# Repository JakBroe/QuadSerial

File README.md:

# QuadSerial
USB Quad Serial Adapter based on FTDI FT4232H chip. 
No firmware needed, the USB driver can be downloaded from https://ftdichip.com/

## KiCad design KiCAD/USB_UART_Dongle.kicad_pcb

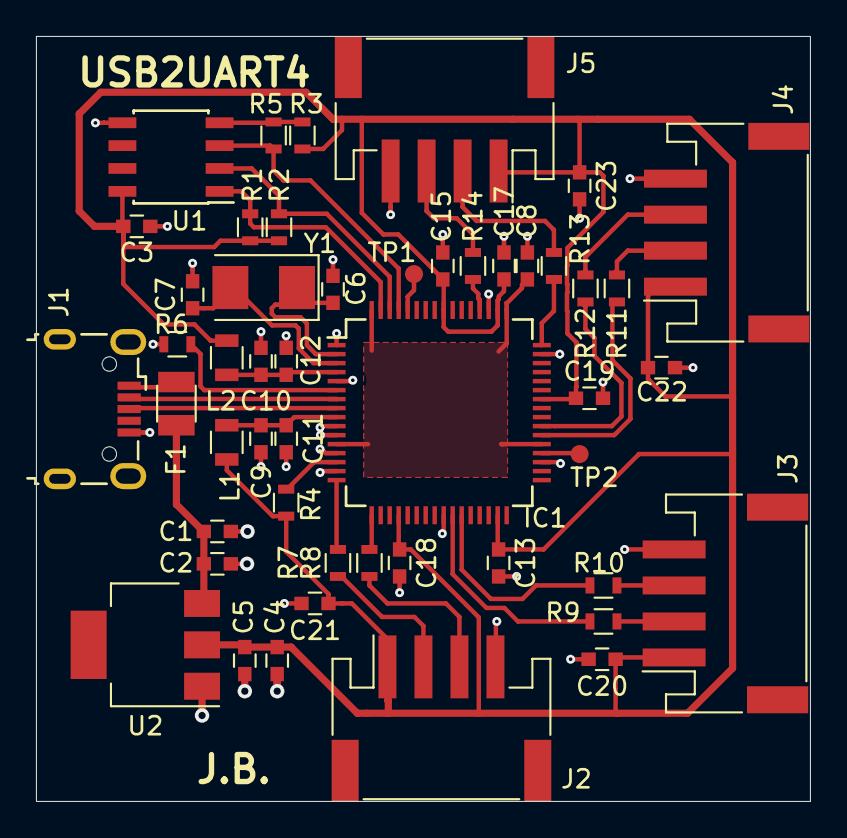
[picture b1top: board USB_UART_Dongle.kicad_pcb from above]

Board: 2 copper layers, 43.0 x 42.5 mm, 49 parts (0 on the bottom side), 35 nets.

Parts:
C1, C5: 1u; C_0603
C2, C3, C4, C11, C12, C13, C15, C17, C18, C19: 100n; C_0603
C6, C7: 27p; C_0603
C8: 3u3; C_0603
C9, C10, C20, C21, C22, C23: 4u7; C_0603
F1: Polyfuse; Fuse_SMD1206_Reflow
IC1: FT4232H; LQFP-64_10x10mm_Pitch0.5mm
J1: USB_B_Micro; USB_Micro-B_Wuerth-629105150521
J2, J3, J4, J5: Conn_01x04; JST_PH_S4B-PH-SM4-TB_04x2.00mm_Angled
L1, L2: L; L_0805
R1, R2, R3: 10k; R_0603
R4, R7, R8, R9, R10, R11, R12, R13, R14: 1k; R_0603
R5: 2k; R_0603
R6: 12k; R_0603
TP1, TP2: TestPoint; Testoint
U1: 93LCxxB; SOIC-8_3.9x4.9mm_Pitch1.27mm
U2: TLV1117-33; SOT-223
Y1: 12MHz; Crystal_SMD_5032-2pin_5.0x3.2mm

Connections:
+1V8: C8.1, IC1.12, IC1.37, IC1.49, IC1.64
+3V3: C3.1, C4.1, C5.1, C13.1, C15.1, C17.1, C18.1, C19.1, C20.1, C21.1, C22.1, C23.1, IC1.20, IC1.31, IC1.42, IC1.50, IC1.56, J2.1, J3.1, J4.1, J5.1, L1.1, L2.1, R1.1, R2.1, R3.1, R4.1, U1.8, U2.2
/DM: IC1.7, J1.2
/DP: IC1.8, J1.3
/RX1: IC1.17, R8.2
/RX2: IC1.27, R10.2
/RX3: IC1.39, R12.2
/RX4: IC1.52, R14.2
/TX1: IC1.16, R7.2
/TX2: IC1.26, R9.2
/TX3: IC1.38, R11.2
/TX4: IC1.48, R13.2
GND: C1.2, C2.2, C3.2, C4.2, C5.2, C6.2, C7.2, C8.2, C9.2, C10.2, C11.2, C12.2, C13.2, C15.2, C17.2, C18.2, C19.2, C20.2, C21.2, C22.2, C23.2, IC1.1, IC1.5, IC1.10, IC1.11, IC1.13, IC1.15, IC1.25, IC1.35, IC1.47, IC1.51, J1.5, J1.6, J2.4, J3.4, J4.4, J5.4, R6.2, U1.5, U2.1
unnamed: C1.1, C2.1, F1.1, U2.3
unnamed: C6.1, IC1.2, Y1.1
unnamed: C7.1, IC1.3, Y1.2
unnamed: C10.1, C12.1, IC1.4, L2.2
unnamed: C9.1, C11.1, IC1.9, L1.2
unnamed: F1.2, J1.1
unnamed: IC1.6, R6.1
unnamed: IC1.14, R4.2
unnamed: IC1.36, TP2.1
unnamed: IC1.60, TP1.1
unnamed: IC1.61, R5.1, U1.3
unnamed: IC1.62, R2.2, U1.2
unnamed: IC1.63, R1.2, U1.1
unnamed: J2.2, R7.1
unnamed: J2.3, R8.1
unnamed: J3.2, R9.1
unnamed: J3.3, R10.1
unnamed: J4.2, R11.1
unnamed: J4.3, R12.1
unnamed: J5.2, R13.1
unnamed: J5.3, R14.1
unnamed: R3.2, R5.2, U1.4

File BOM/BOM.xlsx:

Bezeichner | Wert |  |  |  |  | Link | Status | Link | Preis | Anzahl
> C1, C5 | 1u | Capacitors_SMD:C_0603 | ~ |  |  |  | vorhanden
> C2-C4, C11-C13, C15, C17-C19 | 100n | Capacitors_SMD:C_0603 | ~ |  |  |  | vorhanden
> C6, C7 | 27p | Capacitors_SMD:C_0603 | ~ |  |  |  | Quarz vorhanden
C8 | 3u3 | Capacitors_SMD:C_0603 | ~ |  |  |  | Mouser
> C9, C10, C20-C23 | 4u7 | Capacitors_SMD:C_0603 | ~ |  |  |  | Mouser
F1 | Polyfuse | Fuse_Holders_and_Fuses:Fuse_SMD1206_Reflow | ~ |  |  |  | vorhanden
IC1 | FT4232H | Housings_QFP:LQFP-64_10x10mm_Pitch0.5mm |  |  |  |  | Mouser
J1 | USB_B_Micro | Connectors_USB:USB_Micro-B_Wuerth-629105150521 | ~ |  |  |  | vorhanden
> J2-J5 | Conn_01x04 | Connectors_JST:JST_PH_S4B-PH-SM4-TB_04x2.00mm_Angled | ~
> L1, L2 | L | Inductors_SMD:L_0805 | ~ |  |  | https://www.mouser.de/ProductDetail/80-L0603B100MPWFT | Mouser
> R1-R3 | 10k | Resistors_SMD:R_0603 | ~ |  |  |  | vorhanden
> R4, R7-R14 | 1k | Resistors_SMD:R_0603 | ~ |  |  |  | vorhanden
R5 | 2k | Resistors_SMD:R_0603 | ~ |  |  |  | vorhanden
R6 | 12k | Resistors_SMD:R_0603 | ~ |  |  |  | vorhanden
U1 | 93LCxxB | Housings_SOIC:SOIC-8_3.9x4.9mm_Pitch1.27mm | http://ww1.microchip.com/downloads/en/DeviceDoc/20001749K.pdf |  |  |  | Mouser
U2 | TLV1117-33 | TO_SOT_Packages_SMD:SOT-223 | http://www.ti.com/lit/ds/symlink/tlv1117.pdf |  |  |  | vorhanden
Y1 | 12MHz | Crystals:Crystal_SMD_5032-2pin_5.0x3.2mm | ~ |  |  |  | vorhanden

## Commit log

2022-01-01 image added
